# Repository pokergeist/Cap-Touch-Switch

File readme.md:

# Cap Switch Project

## Introduction

This project aims to create a capacitive touch switch that uses a CR2032 button cell to power a capacitive touch sensor and solid state relay to to assist with switch-adapting a device for assistive technology purposes. The relay is rated at 2A continuous, 40V.

## Status

|    Date    | Status                                                       |
| :--------: | ------------------------------------------------------------ |
| 2023-02-25 | Revising for polarity issue & new JST PH connector. Rev 2b.  |
| 2023-01-12 | All done for now.                                            |
| 2023-01-06 | Boards received, testing underway.                           |
| 2022-12-29 | Boards ordered.                                              |
| 2022-12-27 | Driver circuit simulated. Bench testing and transistor selection pending. |
| 2022-12-23 | Working to support multiple battery options.                 |
| 2022-12-21 | First posting. Untested.                                     |

**2022-02-25**

The Eagle model for the coin cell was wrong and the polarity was backwards so that has been fixed. A JST PH-2 connector (B2.2) option was added. The XH-2 connector (B2.1) was moved into the coin cell (B1) area making them mutually exclusive. Rev 2b.

**2021-01-12**

The new coin cell battery holders arrived and fit perfectly. The current draw test results are [here](board/Current-and-Power-Draw.md).

**2023-01-06**

The boards have been received and (4) boards assembled. What's up:

* The Keystone #1026 button cell holder footprint is wrong (too big) due to their goofy datasheet but moded #103 should fit perfectly since that is what was depicted. Ordering those from Mouser.
* I quickly tested (4) boards with a Lithium pouch (LiPo) cell and the Cap Touch sensor is working fine . I'll be testing with other voltages and testing the SS Relay and capturing video too.
* I need more transistors and relays to populate many more boards, and some new coin cell holders.

**2022-12-27**

A current driver circuit has been selected. See board/[readme](#board/readme.md) file.

**2022-12-23**

I want to test some voltage regulation circuits to see so I can protect the SS Relay (<25mA) while reducing the current (and  power) draw toward the lower level and extending functionality over the range of whatever battery option is used.

## Todo

* Add on-off switch?
* Make sure SSR height (4mm) doesn't interfere with board mounting and sensor access.

## Mounting

The board is intended to be mounted with the cap sensor exposed. There are 3.5mm holes for securing with M3 screws or 3D printed posts.

On the bottom is a button cell holder for (2) CR2016 cells.

## Cap Touch Sensor

## Printed Circuit Board

Please refer to the board/[readme](board/readme.md) file for more info on the PCB.

### TTP223-BA6 Pinout & Modes

| Pin  | Function        |                                                              |
| :--: | --------------- | ------------------------------------------------------------ |
|  1   | Q               | Output pin (open drain).                                     |
|  2   | Vss (GND)       | Ground: 0V                                                   |
|  3   | I               | Input to Oscillator circuit.                                 |
|  4   | TOG (Jumper B)  | 1-Toggle or 0-Momentary mode.                                |
|  5   | Vdd (V+)        | Power: 2.0 - 5.5VDC                                          |
|  6   | AHLB (Jumper A) | Active 1-High or 0-Low output.                               |
|      | LPMB = 0        | Low Power Mode on. (Not Fast Mode)                           |
|      | MOTB = 1        | Max On Time 100s disabled. Infinite On if covered and detected. |
|      | SLRFTB = 1      | Sampling Rate: 1.6ms. Lower current and sensitivity.         |

### Board Jumpers

Leave Jumper A open for an Active High output unless you want to invert the operation of the relay.

Short Jumper B to switch from Momentary mode to Toggle mode.

## Run Time Calculations

| Item                                 | Capacity  / Current Draw | Hours  |
| ------------------------------------ | :----------------------: | :----: |
| Cell Capacity, CR2032                |    240mAh (at 200µA)     |        |
| Cap Touch Board                      |        3µA (max)         | 80,000 |
| Cap Touch Board & SS Relay (3V nom.) |          10.7mA          |  22.4  |

## Battery Options

Provisions for JST XH and PH headers have been added to facilitate the option of using an alternate battery pack. The 2.5mm pitch XH connectors handle bigger wire and are easier to crimp. The 2.0mm pitch PH connectors are common and can be plugged into Feather style microcontroller boards. Because the voltages vary different values for R1 may be necessary.

| Batteries Used                             | Max/Nom/Min Voltages |
| ------------------------------------------ | :------------------: |
| 1 x CR2032                                 |   3.4 / 3.0 / 2.7    |
| 2 x NiCd or NMH (recharable) AA or AAA     |   3.0 / 2.4 / 2.3    |
| 2 x Alkaline AA or AAA                     |    3.3 / 3.0 / ?     |
| 3 x NiCd or NMH (recharable) AA or AAA     |   4.5 / 3.6 / 3.45   |
| 3 x Alkaline AA or AAA                     |    4.95 / 4.5 / ?    |
| 1 x Li-ion (e.g. 18650) or LiPo pouch cell |   4.2 / 3.7 / 2.5    |
| 1 x LiFePO4 (LFP) cell                     |   3.65 / 3.2 / 2.0   |

**Do not use 2 x CR2016 cells** in the button cell holder as that exceeds the maximum voltage of the touch sensor.

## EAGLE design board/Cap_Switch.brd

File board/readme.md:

# Cap Switch Board

## Introduction

This project aims to create a small capacitive touch switch that uses a CR2032 button cell to power a capacitive touch sensor and solid state relay to to assist with switch-adapting a device for assistive technology purposes. The relay is rated at 2A continuous, 40V.

Support for various battery options has been implemented via an external battery jack that can be connected to a battery or battery holder (AA, AAA, NiCd/NMH/Li-ion/LiPo/LiFePO4). Li-ion/LiPo charging via USB could be supported via the addition of a TP4056/DW01 module.

## Status

|    Date    | Status                                                      |
| :--------: | ----------------------------------------------------------- |
| 2023-02-25 | Revising for polarity issue & new JST PH connector. Rev 2b. |
| 2023-01-12 | All done for now.                                           |
| 2023-01-05 | Boards received and assembled. More parts ordered.          |
| 2022-12-29 | Boards ordered.                                             |
| 2022-12-27 | First posting. Untested.                                    |

**2022-02-25**

The Eagle model for the coin cell was wrong and the polarity was backwards so that has been fixed. A JST PH-2 connector (B2.2) option was added. The XH-2 connector (B2.1) was moved into the coin cell (B1) area making them mutually exclusive. Rev 2b.

**2021-01-12**

The new coin cell battery holders arrived and fit perfectly. Voltage and current test results are linked at the bottom.

**2023-01-06**

The boards have been received and (4) boards assembled. What's up:

* The Keystone #1026 button cell footprint is wrong (too big) due to their goofy datasheet, but moded #103 should fit perfectly since that is what was depicted. Ordering those from Mouser.
* I quickly tested (4) boards with a Lithium pouch (LiPo) cell and the Cap Touch sensor is working fine . I'll be testing with other voltages and testing the SS Relay and capturing video too.
* I need more transistors and relays to populate many more boards, and some new coin cell holders.

## Todo

* Add on-off switch?
* Make sure SSR height (4mm) doesn't interfere with board mounting and sensor access.

## Components

Two options are provided for powering this board. Parts for one option or the other could be purchased, or both.

1. a CR2032 "coin"cell
2. some combination of AA, AAA (alkaline or rechargeable NMH) or a Li-ion, Li-Po, or LiFePO4 lithium cell. (Do not exceed the 5.5V maximum voltage of the touch sensor.)

The first will use the coin cell holder, the second will use a JST XH 2.5mm or similar 2.54mm pitch connection option.

| Component                            | Source                                                       | Specs                                                        |
| ------------------------------------ | ------------------------------------------------------------ | ------------------------------------------------------------ |
| Capacitive touch sensor board (S1)   | [HiLetgo TTP223-BA6 Cap Switch](https://smile.amazon.com/dp/B01D1D0FLG) (Amazon ) ([datasheet](../assets/Cap-Touch-TTP223.pdf)) | 2.0-5.5V  3µA max Toggle\|Momentary, Active High\|Low        |
| Solid State Relay (K1)               | [Toshiba TLP241A,TP1](https://www.digikey.com/short/rw8vd8dn) ([datasheet](https://toshiba.semicon-storage.com/info/TLP241A_datasheet_en_20200217.pdf?did=14237&prodName=TLP241A)) | LED: 7.5mA Vf: 1.27V<br>Iout: 2A continuous, 6A pulsed<br>Ron: 90mΩ<br>40V |
| NPN Transistors Q1,Q2                | On Semi [PN2222ABU](https://www.digikey.com/short/n4rrtfnb)  | 40V 1A 625mW                                                 |
| Resistor 1.0 / 2.2 / 3.3kΩ (R1) 1206 | D-K [search](https://www.digikey.com/short/ff9cftjb)         | 1/4W 5% 1206                                                 |
| Resistor 47 - 56Ω (R2) 1206 (*)      | D-K [search](https://www.digikey.com/short/tv9vv7dh)         | 1/4W 5% 1206                                                 |
| Switch Lead Connector                | 0.1" or 2.54mm pitch connector or header posts               |                                                              |
| **Button Cell Option**               |                                                              |                                                              |
| Coin Cell Holder (B1)                | [Keystone #103](https://mou.sr/3W5l7RQ) ([datasheet](https://www.mouser.com/datasheet/2/215/03-745368.pdf)) | 4.5mm standoffs, (1) CR2032<br/> or (2) CR2016 or 2025s      |
| ~~Coin Cell Holder (B1)~~            | ~~[Keystone 1026](https://www.digikey.com/short/f35w9mv4) ([datasheet](https://www.keyelco.com/userAssets/file/M65p3.pdf))~~ | Doesn't fit                                                  |
| CR2032 Coin Cells (B1)               |                                                              | 3V nominal                                                   |
| **External Battery Option**          |                                                              |                                                              |
| External Battery Connector B2.1      | JST [XH header](https://www.digikey.com/short/9hf4mnvj) 2-position, 2.5mm pitch, straight |                                                              |
| External Battery Connector B2.2      | JST [PH header](https://www.digikey.com/short/wp55373q) 2-position, 2.0mm pitch, straight |                                                              |
| Battery Holder Pigtail Connector     | JST [XH housing](https://www.digikey.com/short/7fpfp333) 2-position, 2.5mm pitch |                                                              |
| Pigtail Connector Contacts (x 2)     | JST [XH contact](https://www.digikey.com/short/d91c10q9)     |                                                              |

\* Values need to be verified with test hardware (pending).

Using lower resistance values for R1 will increase the current draw ever so slightly.

Using lower resistance values for R2 will increase the current draw by a meaningful amount.

## Mounting

The board is intended to be mounted with the cap sensor exposed. There are 3.5mm holes for securing with M3 screws or 3D printed posts.

On the bottom is a button cell holder for (1) CR2032 cells.

## Cap Touch Sensor

## Printed Circuit Board

### Top

### Bottom

### Schematic

## TTP223-BA6 Pinout & Modes

| Pin  | Function        |                                                              |
| :--: | --------------- | ------------------------------------------------------------ |
|  1   | Q               | Output pin (open drain).                                     |
|  2   | Vss (GND)       | Ground: 0V                                                   |
|  3   | I               | Input to Oscillator circuit.                                 |
|  4   | TOG (Jumper B)  | 1-Toggle or 0-Momentary mode.                                |
|  5   | Vdd (V+)        | Power: 2.0 - 5.5VDC                                          |
|  6   | AHLB (Jumper A) | Active 1-High or 0-Low output.                               |
|      | LPMB = 0        | Low Power Mode on. (Not Fast Mode)                           |
|      | MOTB = 1        | Max On Time 100s disabled. Infinite On if covered and detected. |
|      | SLRFTB = 1      | Sampling Rate: 1.6ms. Lower current and sensitivity.         |

### Board Jumpers

Leave Jumper A open for an Active High output unless you want to invert the operation of the relay.

Short Jumper B to switch from Momentary mode to Toggle mode.

## Run Time Calculations

| Item                       | Capacity  / Current Draw | Hours  |
| -------------------------- | :----------------------: | :----: |
| Cell Capacity, CR2032      |    240mAh (at 200µA)     |        |
| Cap Touch Board            |        3µA (max)         | 80,000 |
| Cap Touch Board & SS Relay |          10.7mA          |  22.4  |

External battery options will provide considerably longer run times.

## Battery Options

A JST XH socket has been added to provide the option of using an alternate battery pack.

| Batteries Used                             | Max/Nom/Min Voltages (<5.5V!) |
| ------------------------------------------ | :---------------------------: |
| 1 x CR2032                                 |        3.4 / 3.0 / 2.7        |
| 2 x NiCd or NMH (recharable) AA or AAA     |        3.0 / 2.4 / 2.3        |
| 2 x Alkaline AA or AAA                     |         3.3 / 3.0 / ?         |
| 3 x NiCd or NMH (recharable) AA or AAA     |       4.5 / 3.6 / 3.45        |
| 3 x Alkaline AA or AAA                     |        4.95 / 4.5 / ?         |
| 1 x Li-ion (e.g. 18650) or LiPo pouch cell |        4.2 / 3.7 / 2.5        |
| 1 x LiFePO4 (LFP) cell                     |       3.65 / 3.2 / 2.0        |

**Do not use 2 x CR2016 cells** in the button cell holder as that exceeds the maximum voltage of the touch sensor.

## LED Current Driver

This 2-transistor current driver will maintain the SS Relay optical input current at about 10mA across the input voltage range of 2.0 to 4.5V. The circuit is simulated at [Falstad circuit.js](https://tinyurl.com/2kyk5f8h) with sliders on the right for input voltage and the collector resistor value. There's an ammeter and voltage probe for the LED.

The top transistor will conduct current until the voltage drop across the 56Ω resistor approaches 0.7V, turning on the lower transistor. As the lower transistor turns on it will start pulling the base of the upper transistor to ground, turning off the upper transistor which will reduce the LED current to an equilibrium point.

## Voltage, Current, & Power Measurements

Measurements were taken using input voltages from 1.5 (the minimum) to 5.0V. The greatest efficiency is at low votage where the sensor's LED is barely on and the power lost at Q1 is minimal.

The measurement log is [here](Current-and-Power-Draw.md).

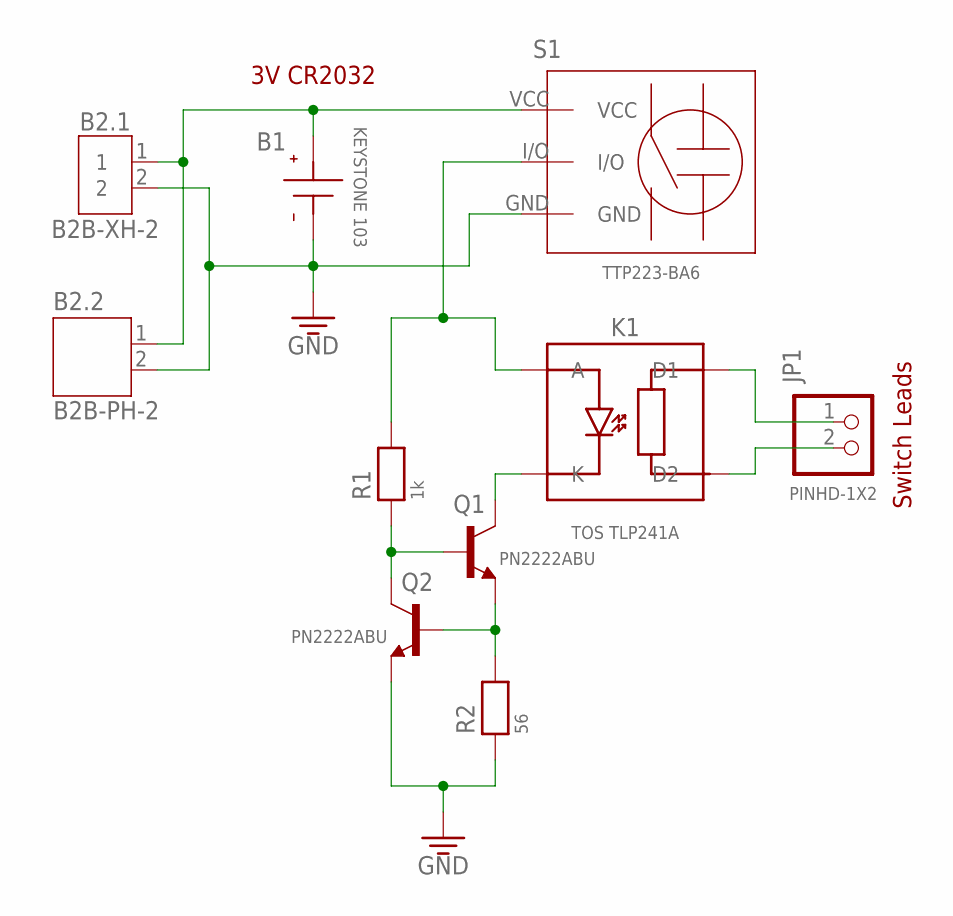
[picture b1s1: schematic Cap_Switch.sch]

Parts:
B1: KEYSTONE 103; 1026_KEY-103
B2.1: B2B-XH-2; B2B-XH-A
B2.2: B2B-PH-2; JST-PH2
JP1: PINHD-1X2; 1X02
K1: TOS TLP241A; TOS-TLP241A
Q1, Q2: PN2222ABU; TO92-
R1: 1k; 1206
R2: 56; 1206
S1: TTP223-BA6; SW-CAP-TOUCH-AMZN

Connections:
GND: B1.- (NEG), B2.1.2, B2.2.2, Q2.1 (E), R2.1, S1.GND
K: K1.P$2 (K), Q1.3 (C)
Q1-DRIVE: Q1.2 (B), Q2.3 (C), R1.1
Q2-DRIVE: Q1.1 (E), Q2.2 (B), R2.2
SW-A: JP1.1, K1.P$4 (D1)
SW-B: JP1.2, K1.P$3 (D2)
TRIGGER: K1.P$1 (A), R1.2, S1.I/O
V+: B1.+ (POS), B2.1.1, B2.2.1, S1.VCC

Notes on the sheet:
3V CR2032
Switch Leads

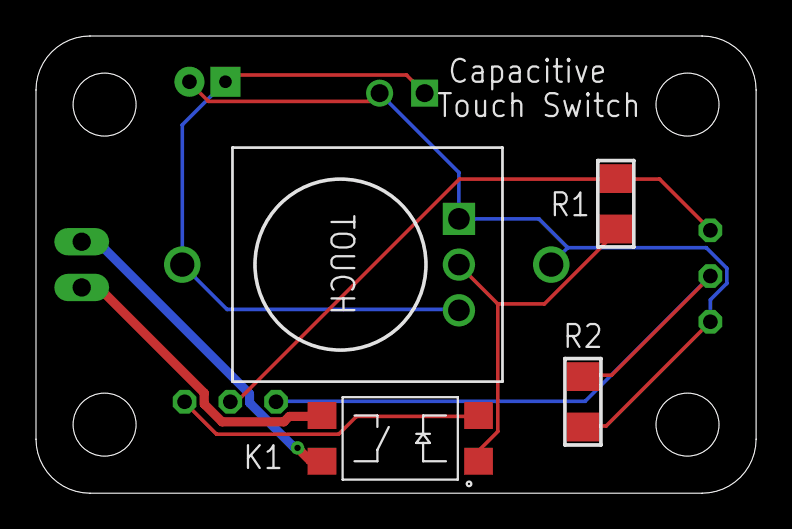
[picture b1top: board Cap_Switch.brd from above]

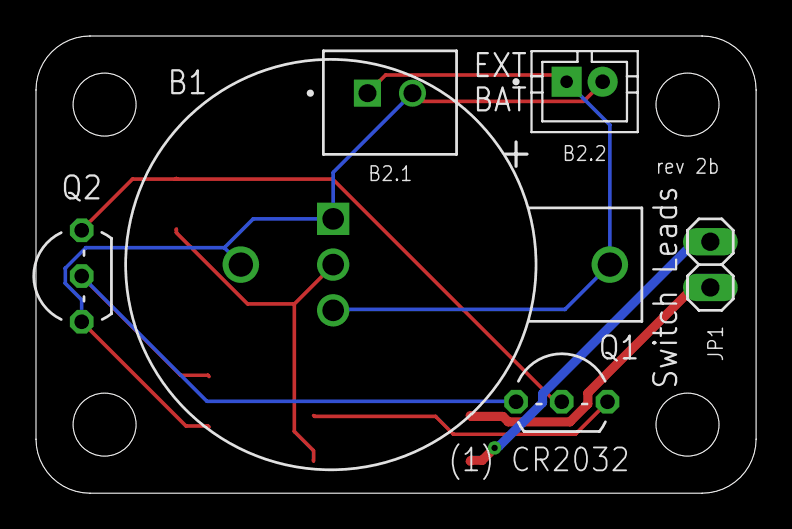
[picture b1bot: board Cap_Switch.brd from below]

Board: 2 copper layers, 40.0 x 25.4 mm, 10 parts (6 on the bottom side), 8 nets.

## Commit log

2022-12-22 first ci
2022-12-22 renamed
2022-12-22 resized
2022-12-22 schematic
2022-12-22 lots more info
2022-12-22 ext battery options
2022-12-27 LED driver circuit
2022-12-27 board files
2022-12-27 corrections
2022-12-29 boards orderedd
2023-01-06 parts & status update
2023-01-06 images
2023-01-06 resized img
2023-01-07 current measurements
2023-01-09 battery lead plug
2023-01-09 plug contacts
2023-01-12 status update
2023-02-25 fixed coin cell polarity, new PH con
2023-02-25 +PH-2 header

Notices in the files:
parts and their libraries:
microbuilder: This work is placed in the public domain, and may be freely used for commercial and non-commercial work with the following conditions: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
COPYRIGHT: Copyright (C) 2022 Ultra Librarian. All rights reserved.
